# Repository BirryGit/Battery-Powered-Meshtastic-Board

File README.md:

# Battery-Powered-Meshtastic-Board
This is an ESP-32-S3 powered LoRa board with a battery charger. It has a connected screen and external pins for I2C and power outputs. It has ESD protection.

I want to learn how to make PCBs, and this seemed like a good idea. I wanted to make my first PCB and understand the whole process. I want to get into meshtastic, so this is awesome :)

# BOM
| Name | Purpose | Quantity | Total Cost (USD) | Link | Distributor |
|---|---|---:|---:|---|---|
| PCB | Puts Everything Together | 1 | 22.48 | https://jlcpcb.com  | JLCPCB |
| 10µF | C14 | 1 | 1.48 | https://www.digikey.com/en/mylists/list/BA1MMOEV0W/quote/18716729 | Digikey |
| LTST-C190TBKT | Leds | 3 | 1.73 | https://www.digikey.com/en/mylists/list/BA1MMOEV0W/quote/18716729 | Digikey |
| 5.1K | R1,R2 | 2 | 0.47 | https://www.digikey.com/en/mylists/list/BA1MMOEV0W/quote/18716729 | Digikey |
| 1M | R6 | 1 | 0.47 | https://www.digikey.com/en/mylists/list/BA1MMOEV0W/quote/18716729 | Digikey |
| 200k | R7 | 1 | 0.47 | https://www.digikey.com/en/mylists/list/BA1MMOEV0W/quote/18716729 | Digikey |
| 1k | R9,R10,R11 | 3 | 0.47 | https://www.digikey.com/en/mylists/list/BA1MMOEV0W/quote/18716729 | Digikey |
| BQ24040DSQR | Battery Charger | 1 | 2.85 | https://www.digikey.com/en/mylists/list/BA1MMOEV0W/quote/18716729 | Digikey |
| TLV75801PDRV | Linear Regulator | 1 | 0.93 | https://www.digikey.com/en/mylists/list/BA1MMOEV0W/quote/18716729 | Digikey |
| Buttons | Boot1,Reset1 | 2 | 0.00 | |  |
| ESP32-S3-WROOM-1 | Processor | 1 | 11.76 | https://www.digikey.com/en/mylists/list/BA1MMOEV0W/quote/18716729 | Digikey |
| 0.1µF | C13,C15 | 2 | 0.73 | https://www.digikey.com/en/mylists/list/BA1MMOEV0W/quote/18716729 | Digikey |
| USB4105-GF-A | USB C Port | 1 | 2.40 | https://www.digikey.com/en/mylists/list/BA1MMOEV0W/quote/18716729 | Digikey |
| 10k | R4,R5 | 2 | 0.47 | https://www.digikey.com/en/mylists/list/BA1MMOEV0W/quote/18716729 | Digikey |
| 540 | R8 | 1 | 0.47 | https://www.digikey.com/en/mylists/list/BA1MMOEV0W/quote/18716729 | Digikey |
| ESD7104MUTAG | ESD Protection | 1 | 3.15 | https://www.digikey.com/en/mylists/list/BA1MMOEV0W/quote/18716729 | Digikey |
| 1µF | C9,C10,C11,C12 | 4 | 2.75 | https://www.digikey.com/en/mylists/list/BA1MMOEV0W/quote/18716729 | Digikey |
| Wio-SX1262 | LoRa Module | 1 | 8.58 | https://www.seeedstudio.com/Wio-SX1262-Wireless-Module-p-5981.html | Seeed Studio |

# Pictures

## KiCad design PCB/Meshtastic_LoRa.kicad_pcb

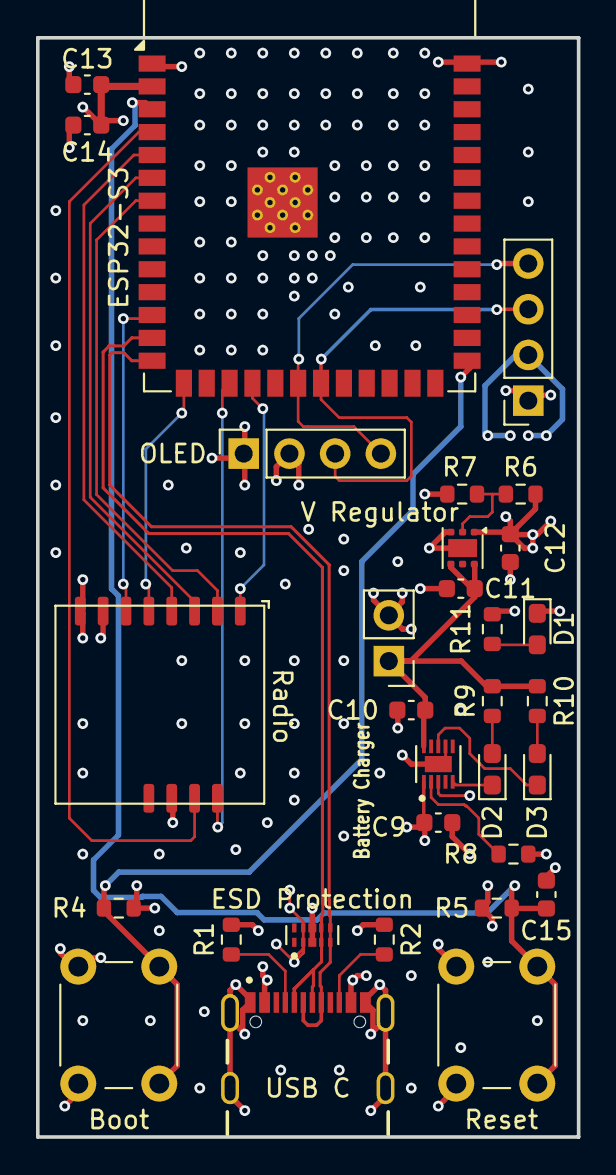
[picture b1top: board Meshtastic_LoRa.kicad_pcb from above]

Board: 4 copper layers, 30.0 x 61.1 mm, 31 parts (0 on the bottom side), 27 nets.

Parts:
Battery1: Conn_01x02_Socket; PinHeader_1x02_P2.54mm_Vertical
Battery Charger: BQ24040DSQR; SON40P200X200X80-11N
Boot: SW_Push; SW_PUSH_6mm
C9, C10, C11, C12: 1µF; C_0603_1608Metric
C13, C15: 0.1µF; C_0603_1608Metric
C14: 10µF; C_0603_1608Metric
D1, D2, D3: LED; LED_0603_1608Metric_Pad1.05x0.95mm_HandSolder
ESD Protection: ESD7104MUTAG; IC_ESD7104MUTAG
ESP32-S3: ESP32-S3-WROOM-1
OLED: Conn_01x04_Socket; PinSocket_1x04_P2.54mm_Vertical
Output1: Extra Output; PinSocket_1x04_P2.54mm_Vertical
R1, R2: 5.1K; R_0603_1608Metric
R4, R5: 10k; R_0603_1608Metric
R6: 1M; R_0603_1608Metric
R7: 200k; R_0603_1608Metric
R8: 540; R_0603_1608Metric
R9, R10, R11: 1k; R_0603_1608Metric
Radio: Value; Wio-SX1262 PCB Package
Reset: SW_Push; SW_PUSH_6mm
USB C: USB4105-GF-A; GCT_USB4105-GF-A
V Regulator: TLV75801PDRV; WSON-6-1EP_2x2mm_P0.65mm_EP1x1.6mm

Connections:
+3V3: C12.2, C13.2, C14.2, ESP32-S3.2 (3V3), OLED.2, Output1.2, R4.2, R5.2, R6.1, R11.1, Radio.8 (VCC), V Regulator.1 (OUT)
+5V: Battery Charger.1 (IN), C9.2, ESD Protection.2 (I/O_2), ESD Protection.9, USB C.A4_B9 (VBUS), USB C.B4_A9 (VBUS)
+BATT: Battery1.1, Battery Charger.10 (OUT), C10.2, C11.2, R9.1, R10.1, V Regulator.4 (EN), V Regulator.6 (IN)
/BUSY: ESP32-S3.4 (IO4), Radio.11 (BUSY)
/D+: ESD Protection.5 (I/O_5), ESD Protection.6, ESP32-S3.14 (USB_D+), USB C.A6 (DP1), USB C.B6 (DP2)
/D-: ESD Protection.4 (I/O_4), ESD Protection.7, ESP32-S3.13 (USB_D-), USB C.A7 (DN1), USB C.B7 (DN2)
/DIO1: ESP32-S3.17 (IO9), Radio.12 (DIO1)
/MISO: ESP32-S3.7 (IO7), Radio.2 (MISO)
/MOSI: ESP32-S3.6 (IO6), Radio.3 (MOSI)
/NSS: ESP32-S3.12 (IO8), Radio.6 (NSS)
/RESET: ESP32-S3.15 (IO3), Radio.5 (RST)
/RF_SW1: ESP32-S3.18 (IO10), Radio.1 (RF_SW1)
/SCK: ESP32-S3.5 (IO5), Radio.4 (SCK)
/SCL: ESP32-S3.21 (IO13), OLED.3, Output1.3
/SDA: ESP32-S3.20 (IO12), OLED.4, Output1.4
GND: Battery1.2, Battery Charger.3 (VSS), Battery Charger.7 (ISET2), Battery Charger.11 (EXP), Boot.1, C9.1, C10.1, C11.1, C12.1, C13.1, C14.1, C15.2, D1.1 (K), ESD Protection.3 (GND), ESD Protection.8 (GND__1), ESP32-S3.1 (GND), ESP32-S3.40 (GND), ESP32-S3.41 (GND), OLED.1, Output1.1, R1.1, R2.2, R7.2, R8.2, Radio.7 (GND1), Radio.10 (GND2), Reset.1, USB C.A1_B12 (GND), USB C.B1_A12 (GND), USB C.SH1 (SHELL_GND), USB C.SH2 (SHELL_GND), USB C.SH3 (SHELL_GND), USB C.SH4 (SHELL_GND), V Regulator.3 (GND), V Regulator.7 (GND)
unnamed: D1.2 (A), R11.2
unnamed: D2.2 (A), R9.2
unnamed: Battery Charger.5 (~PG), D2.1 (K)
unnamed: D3.2 (A), R10.2
unnamed: Battery Charger.8 (~CHG), D3.1 (K)
unnamed: R1.2, USB C.A5 (CC1)
unnamed: R2.1, USB C.B5 (CC2)
unnamed: C15.1, ESP32-S3.3 (EN), R5.1, Reset.2
unnamed: Boot.2, ESP32-S3.27 (IO0), R4.1
unnamed: Battery Charger.2 (ISET), R8.1
unnamed: R6.2, R7.1, V Regulator.2 (FB)

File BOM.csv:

Name,Purpose,Quantity,Total Cost (USD),Link,Distributor
"PCB","Puts Everything Together",1,22.48,"","JLCPCB"
"10µF","C14",1,1.48,"https://www.digikey.com/en/mylists/list/BA1MMOEV0W/quote/18716729","Digikey"
"LTST-C190TBKT","Leds",3,1.73,"https://www.digikey.com/en/mylists/list/BA1MMOEV0W/quote/18716729","Digikey"
"5.1K","R1,R2",2,0.47,"https://www.digikey.com/en/mylists/list/BA1MMOEV0W/quote/18716729","Digikey"
"1M","R6",1,0.47,"https://www.digikey.com/en/mylists/list/BA1MMOEV0W/quote/18716729","Digikey"
"200k","R7",1,0.47,"https://www.digikey.com/en/mylists/list/BA1MMOEV0W/quote/18716729","Digikey"
"1k","R9,R10,R11",3,0.47,"https://www.digikey.com/en/mylists/list/BA1MMOEV0W/quote/18716729","Digikey"
"BQ24040DSQR","Battery Charger",1,2.85,"https://www.digikey.com/en/mylists/list/BA1MMOEV0W/quote/18716729","Digikey"
"TLV75801PDRV","Linear Regulator",1,0.93,"https://www.digikey.com/en/mylists/list/BA1MMOEV0W/quote/18716729","Digikey"
"Buttons","Boot1,Reset1",2,0.00,"https://jlcpcb.com",""
"ESP32-S3-WROOM-1","Processor",1,11.76,"https://www.digikey.com/en/mylists/list/BA1MMOEV0W/quote/18716729","Digikey"
"0.1µF","C13,C15",2,0.73,"https://www.digikey.com/en/mylists/list/BA1MMOEV0W/quote/18716729","Digikey"
"USB4105-GF-A","USB C Port",1,2.40,"https://www.digikey.com/en/mylists/list/BA1MMOEV0W/quote/18716729","Digikey"
"10k","R4,R5",2,0.47,"https://www.digikey.com/en/mylists/list/BA1MMOEV0W/quote/18716729","Digikey"
"540","R8",1,0.47,"https://www.digikey.com/en/mylists/list/BA1MMOEV0W/quote/18716729","Digikey"
"ESD7104MUTAG","ESD Protection",1,3.15,"https://www.digikey.com/en/mylists/list/BA1MMOEV0W/quote/18716729","Digikey"
"1µF","C9,C10,C11,C12",4,2.75,"https://www.digikey.com/en/mylists/list/BA1MMOEV0W/quote/18716729","Digikey"
"Wio-SX1262","LoRa Module",1,8.58,"https://www.seeedstudio.com/Wio-SX1262-Wireless-Module-p-5981.html","Seeed Studio"

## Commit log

2026-05-27 Added Gerber Files
2026-05-27 Rename Meshtastic_LoRa-job.gbrjob to gerber/Meshtastic_LoRa-job.gbrjob
2026-05-27 Rename Meshtastic_LoRa-B_Cu.gbr to gerber/Meshtastic_LoRa-B_Cu.gbr
2026-05-27 Rename Meshtastic_LoRa-B_Mask.gbr to gerber/Meshtastic_LoRa-B_Mask.gbr
2026-05-27 Moved the rest of the files to gerber
2026-05-27 Added Schematic and PCB
2026-05-27 Added BOM
2026-05-27 Updated Readme
    Added a detailed description of the battery-powered LoRa board and included a Bill of Materials (BOM) with component details.
2026-05-27 Added Firmware
2026-05-27 Moved Firmware
2026-05-27 Add pictures section to README
    Added images to the README for better visualization.
